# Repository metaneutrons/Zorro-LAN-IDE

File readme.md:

# Zorro-LAN-IDE
 
This is a Zorro-expansion card for the big Amigas (A2000/300/4000 or A500 with Zorro-interface). It has a SANAII-compatible Ethernet driver, an AT-BUS compatible IDE controller and a clockport for variuous expansions like a RapidRoard from Individual Computers.

Here is a pic of the first revision:

All components are Autoconfig. The FastEthernet is based on a ENC624J600 lan chip. The clockport is compatible to A600/A1200 ones but resides at a different address. The IDE works from Kickstart 1.3 to 3.1.4 !

At present there are two firmwares: One for Zorro2, which runs in every Amiga with Zorro-Sots and one for A3000/4000, which puts the LAN-Chip into a Zorro3 environment. The while the Zorro2 variant can transfer 3.5mb/s at most the Zorro3-variant has a significantly faster LAN<->Amiga interface of 6-7mb/sec. Please note that these RAW data transfer numbers are not the only factor in LAN performance on Amiga and that the actual observed speeds with TCP transfers are in the range of 1-2 MB/s (depending on IP stack and CPU). 

Here is a pic of the current board revision:

## Things to improve

* The second revision already adresses the issues of the Zorro3-incompatible IDE-Interface.
* There is no Z2/Z3 combo firmware, yet.
* The RJ45-breakout (actually it's a MagJack with build in transceiver) of the 2nd revision looks bad 

**DISCLAIMER!!!!**  
**THIS IS A HOBBYIST PROJECT! I'M NOT RESPONSIBLE IF IT DOESN'T WORK OR DESTROYS YOUR VALUABLE DATA!**

## License
All sources published under GNU GENERAL PUBLIC LICENSE V2.0

## Theory of operation
* This PCB has four layers and consists of a Xilinx XC95288XL, a bootrom and some bus bufferes for the IDE port, a clockport and a ENC624J600 including a RJ45-connector with integrated receiver. 

* The CPLD does four things:
    * It makes the Autoconfig for the IDE, the clockport and the LAN-chip
    * It adapts the LAN Chip to Zorro2/3 and does necessary byte swapping, so the Amiga can linearely access the whole chip.
    * It acesses the clockport
    * It controlls the IDE

## How to make the clockport work with a RapidRoad?

Make sure you connected the cable the right way! There is no "standarized way". So the easiest thing is to find out on the RapidRoad side on which row of the clockport the two outer pins are ground. These Pins mus run to the row of the Zorro-LAN-IDE-CP-card where the squared solder-hole is located. *Please triple check the cable with a multimeter! Wrong polarity of the cable can cause damage to your hardware!* 
Now you have to set up the driver to look for a clockport at the address of the expansion board. The address can be figured out by the system tool "ShowConfig" (Manufactor id: 2588 Product: 124). 
However, there is work on a software solution, that the RapidRoad finds itself automatically!

## What is in this repository?
This repository consists of several directories:

* Bilder: Some pictures of this project
* Doku: Some documentation and datasheets. Mainly for the ENC624J600
* Driver: Here is the driver developped by Henryk Richter
* Logic: Here the code, project files and pin-assignments for the CPLD is stored. There are two versions: 
* PCB: The board, schematic and bill of material (BOM) are in this directory. 
* root directory: the readme

## How to open the PCB-files?
You find the eagle board and schematic files (brd/sch) for the pcb. The software can be [downloaded](https://www.autodesk.com/products/eagle/overview) for free after registration. KiCad can import these files too. But importers are not 100% reliable... 

## How to make a PCB?
You can generate Gerber-files from the brd files according to the specs of your PCB-manufactor. Some specs: min trace width: 0.15mm/6mil, min trace dist: 0.15mm/6mil, min drill: 0.3mm

**ATTENTION: THE PCB has 4 layers!**

## How to get the parts?
Most parts can be found on digikey or mouser or a parts supplier of your choice.
A list of parts is found in the file [ZORRO-LAN-IDE-CP-V2E.txt](https://gitlab.com/MHeinrichs/Zorro-LAN-IDE/raw/master/PCB/ZORRO-LAN-IDE-CP-V2E.txt)

## How to programm the board?
The CPLD must be programmed via Xilinx IMPACT and an apropriate JTAG-dongle. The JED-File is provided. 

## It doesn't work! How to I get help?
For support visit the [a1k-forum](https://www.a1k.org/forum/showthread.php?t=56940). Yes, you need to register and it's German, but writing in English is accepted. For bug-reports write a ticket here ;).

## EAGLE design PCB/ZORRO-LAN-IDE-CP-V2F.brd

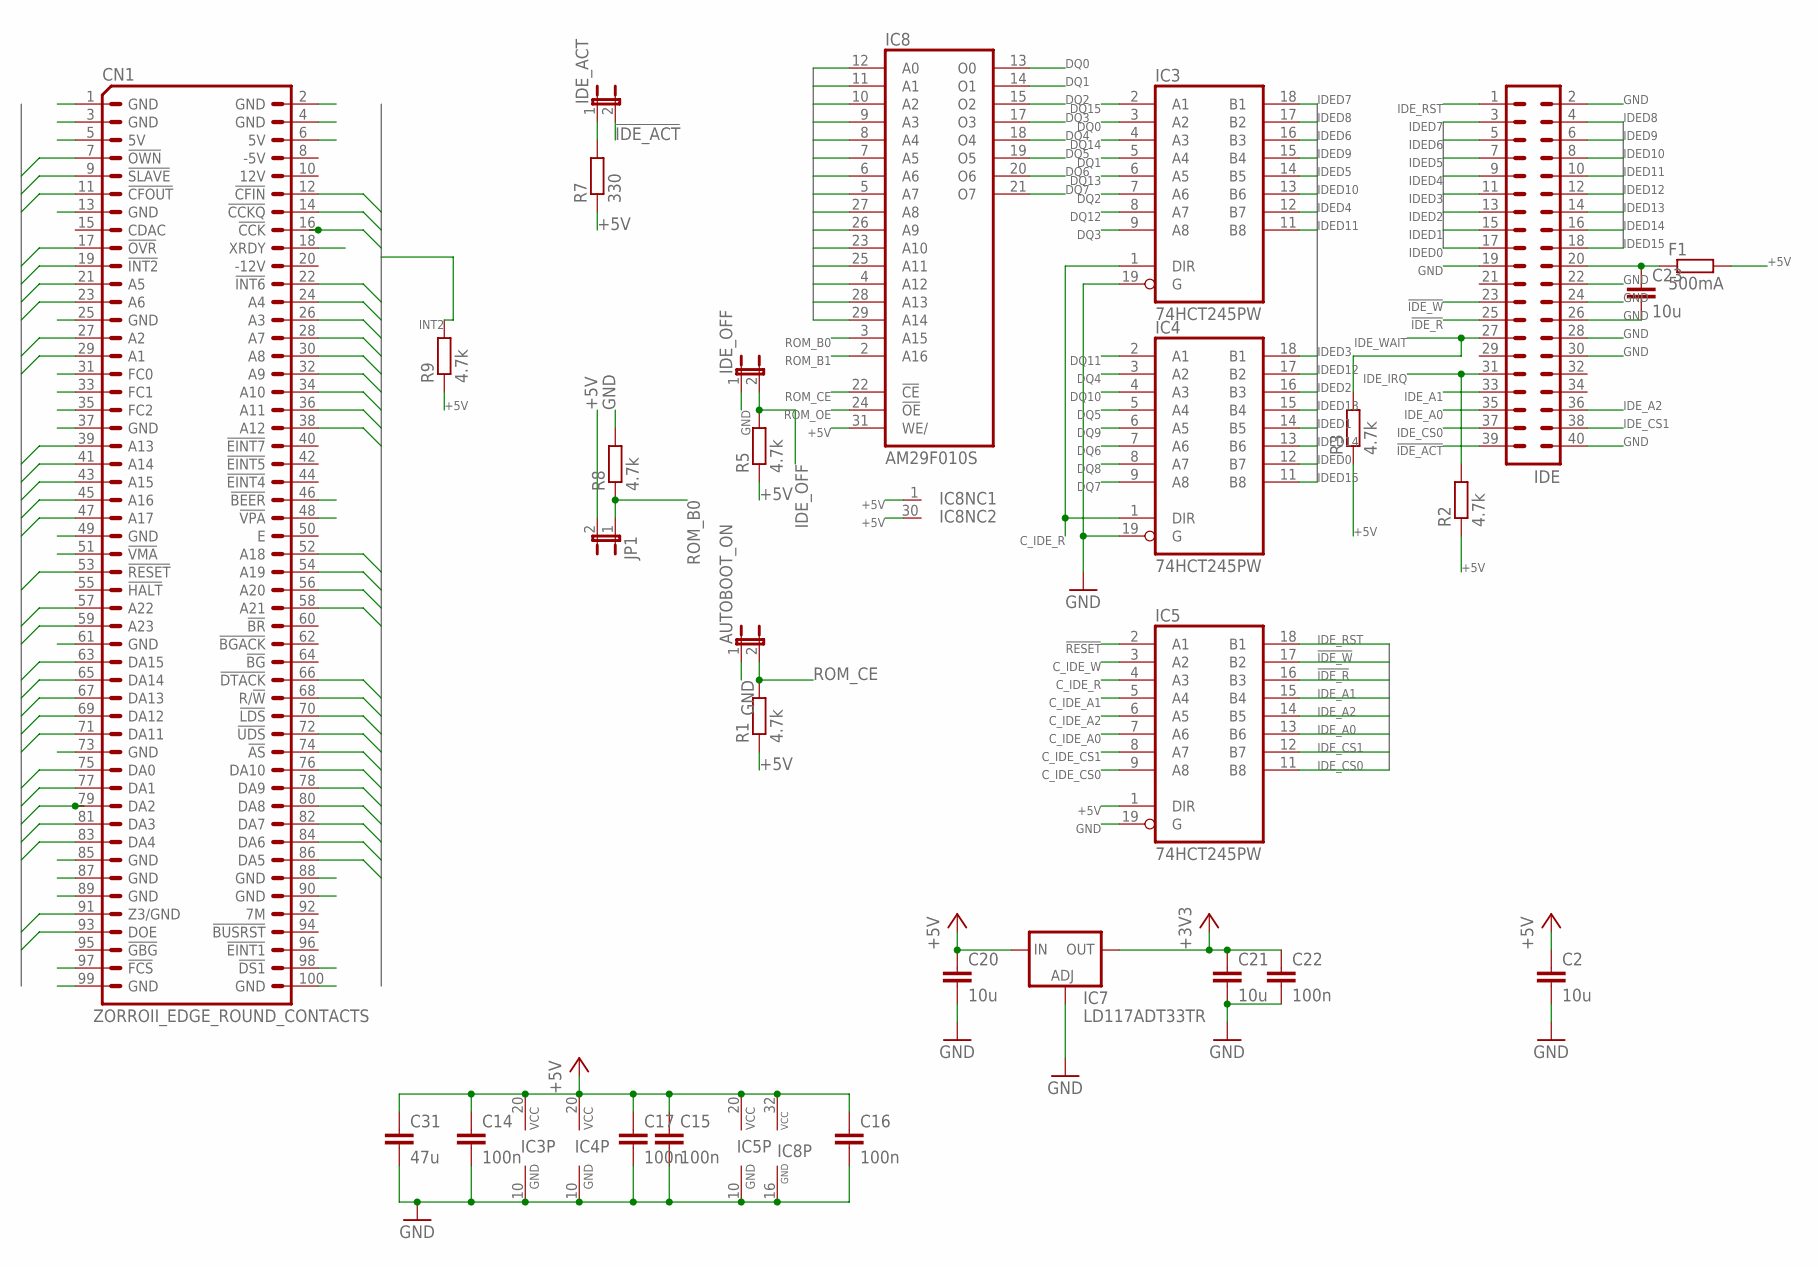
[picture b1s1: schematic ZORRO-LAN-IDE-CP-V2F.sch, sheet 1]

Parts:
AUTOBOOT_ON: JP1E; JP1
C2, C23: 10u; C0805K
C14, C15, C16, C17, C22: 100n; C0603K
C20: 10u; C1206K
C21: 10u; C1210K
C31: 47u; C1206K
CN1: ZORROII_EDGE_ROUND_CONTACTS; LKONT_50_R
F1: 500mA; R2512
IC3, IC4, IC5: 74HCT245PW; TSSOP20
IC7: LD117ADT33TR; DPACK
IC8: AM29F010S; PLCC-SR32
IDE: ML40
IDE_ACT: JP1E; JP1
IDE_OFF: JP1E; JP1
JP1: JP1E; JP1
R1, R2, R3, R5, R8, R9: 4.7k; R0603
R7: 330; R0603

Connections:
!AS: CN1.74 (!AS!); also elsewhere on the board
!BERR: CN1.46 (!BEER!); also elsewhere on the board
!CFIN: CN1.12 (!CFIN!); also elsewhere on the board
!CFOUT: CN1.11 (!CFOUT!); also elsewhere on the board
!DS0: CN1.51 (!VMA!); also elsewhere on the board
!DS1: CN1.98 (!DS1!); also elsewhere on the board
!DTACK: CN1.66 (!DTACK!); also elsewhere on the board
!FCS: CN1.97 (!FCS!); also elsewhere on the board
!IDE_ACT: IDE.39, IDE_ACT.2
!IDE_R: IC5.16 (B3), IDE.25
!IDE_W: IC5.17 (B2), IDE.23
!LDS: CN1.70 (!LDS!); also elsewhere on the board
!MTACK: CN1.48 (!VPA!); also elsewhere on the board
!MTCR: CN1.18 (XRDY); also elsewhere on the board
!OVR: CN1.17 (!OVR!); also elsewhere on the board
!OWN: CN1.7 (!OWN!); also elsewhere on the board
!RESET: CN1.53 (!RESET!), IC5.2 (A1); also elsewhere on the board
!SLAVE: CN1.9 (!SLAVE!); also elsewhere on the board
!UDS: CN1.72 (!UDS!); also elsewhere on the board
+3V3: C21.1, C22.1, IC7.4 (OUT); also elsewhere on the board
+5V: C2.1, C14.1, C15.1, C16.1, C17.1, C20.1, C31.1, CN1.5 (5V), CN1.6 (5V), F1.2, IC3.20 (VCC), IC4.20 (VCC), IC5.1 (DIR), IC5.20 (VCC), IC7.3 (IN), IC8.1 (NC), IC8.30 (NC), IC8.31 (WE/), IC8.32 (VCC), JP1.2, R1.1, R2.1, R3.1, R5.1, R7.1, R9.1; also elsewhere on the board
A1: CN1.29 (A1), IC8.12 (A0); also elsewhere on the board
A2: CN1.27 (A2), IC8.11 (A1); also elsewhere on the board
A3: CN1.26 (A3), IC8.10 (A2); also elsewhere on the board
A4: CN1.24 (A4), IC8.9 (A3); also elsewhere on the board
A5: CN1.21 (A5), IC8.8 (A4); also elsewhere on the board
A6: CN1.23 (A6), IC8.7 (A5); also elsewhere on the board
A7: CN1.28 (A7), IC8.6 (A6); also elsewhere on the board
A8: CN1.30 (A8), IC8.5 (A7); also elsewhere on the board
A9: CN1.32 (A9), IC8.27 (A8); also elsewhere on the board
A10: CN1.34 (A10), IC8.26 (A9); also elsewhere on the board
A11: CN1.36 (A11), IC8.23 (A10); also elsewhere on the board
A12: CN1.38 (A12), IC8.25 (A11); also elsewhere on the board
A13: CN1.39 (A13), IC8.4 (A12); also elsewhere on the board
A14: CN1.41 (A14), IC8.28 (A13); also elsewhere on the board
A15: CN1.43 (A15), IC8.29 (A14); also elsewhere on the board
A16: CN1.45 (A16); also elsewhere on the board
A17: CN1.47 (A17); also elsewhere on the board
A18: CN1.52 (A18); also elsewhere on the board
A19: CN1.54 (A19); also elsewhere on the board
A20: CN1.56 (A20); also elsewhere on the board
A21: CN1.58 (A21); also elsewhere on the board
A22: CN1.57 (A22); also elsewhere on the board
A23: CN1.59 (A23); also elsewhere on the board
C1: CN1.14 (!CCKQ!); also elsewhere on the board
C3: CN1.16 (!CCK!); also elsewhere on the board
C_IDE_A0: IC5.7 (A6); also elsewhere on the board
C_IDE_A1: IC5.5 (A4); also elsewhere on the board
C_IDE_A2: IC5.6 (A5); also elsewhere on the board
C_IDE_CS0: IC5.9 (A8); also elsewhere on the board
C_IDE_CS1: IC5.8 (A7); also elsewhere on the board
C_IDE_R: IC3.1 (DIR), IC4.1 (DIR), IC5.4 (A3); also elsewhere on the board
C_IDE_W: IC5.3 (A2); also elsewhere on the board
D0: CN1.75 (DA0); also elsewhere on the board
D1: CN1.77 (DA1); also elsewhere on the board
D2: CN1.79 (DA2); also elsewhere on the board
D3: CN1.81 (DA3); also elsewhere on the board
D4: CN1.83 (DA4); also elsewhere on the board
D5: CN1.86 (DA5); also elsewhere on the board
D6: CN1.84 (DA6); also elsewhere on the board
D7: CN1.82 (DA7); also elsewhere on the board
D8: CN1.80 (DA8); also elsewhere on the board
D9: CN1.78 (DA9); also elsewhere on the board
D10: CN1.76 (DA10); also elsewhere on the board
D11: CN1.71 (DA11); also elsewhere on the board
D12: CN1.69 (DA12); also elsewhere on the board
D13: CN1.67 (DA13); also elsewhere on the board
D14: CN1.65 (DA14); also elsewhere on the board
D15: CN1.63 (DA15); also elsewhere on the board
DOE: CN1.93 (DOE); also elsewhere on the board
DQ0: IC3.3 (A2), IC8.13 (O0); also elsewhere on the board
DQ1: IC3.5 (A4), IC8.14 (O1); also elsewhere on the board
DQ2: IC3.7 (A6), IC8.15 (O2); also elsewhere on the board
DQ3: IC3.9 (A8), IC8.17 (O3); also elsewhere on the board
DQ4: IC4.3 (A2), IC8.18 (O4); also elsewhere on the board
DQ5: IC4.5 (A4), IC8.19 (O5); also elsewhere on the board
DQ6: IC4.7 (A6), IC8.20 (O6); also elsewhere on the board
DQ7: IC4.9 (A8), IC8.21 (O7); also elsewhere on the board
DQ8: IC4.8 (A7); also elsewhere on the board
DQ9: IC4.6 (A5); also elsewhere on the board
DQ10: IC4.4 (A3); also elsewhere on the board
DQ11: IC4.2 (A1); also elsewhere on the board
DQ12: IC3.8 (A7); also elsewhere on the board
DQ13: IC3.6 (A5); also elsewhere on the board
DQ14: IC3.4 (A3); also elsewhere on the board
DQ15: IC3.2 (A1); also elsewhere on the board
FC0: CN1.31 (FC0)
FC1: CN1.33 (FC1)
FC2: CN1.35 (FC2)
GND: AUTOBOOT_ON.1, C2.2, C14.2, C15.2, C16.2, C17.2, C20.2, C21.2, C22.2, C23.2, C31.2, CN1.1 (GND), CN1.2 (GND), CN1.3 (GND), CN1.4 (GND), CN1.13 (GND), CN1.25 (GND), CN1.37 (GND), CN1.49 (GND), CN1.61 (GND), CN1.73 (GND), CN1.85 (GND), CN1.87 (GND), CN1.88 (GND), CN1.89 (GND), CN1.90 (GND), CN1.99 (GND), CN1.100 (GND), IC3.10 (GND), IC3.19 (G), IC4.10 (GND), IC4.19 (G), IC5.10 (GND), IC5.19 (G), IC7.1 (ADJ), IC8.16 (GND), IDE.2, IDE.19, IDE.22, IDE.24, IDE.26, IDE.28, IDE.30, IDE.40, IDE_OFF.1, R8.2; also elsewhere on the board
IDED0: IC4.12 (B7), IDE.17
IDED1: IC4.14 (B5), IDE.15
IDED2: IC4.16 (B3), IDE.13
IDED3: IC4.18 (B1), IDE.11
IDED4: IC3.12 (B7), IDE.9
IDED5: IC3.14 (B5), IDE.7
IDED6: IC3.16 (B3), IDE.5
IDED7: IC3.18 (B1), IDE.3
IDED8: IC3.17 (B2), IDE.4
IDED9: IC3.15 (B4), IDE.6
IDED10: IC3.13 (B6), IDE.8
IDED11: IC3.11 (B8), IDE.10
IDED12: IC4.17 (B2), IDE.12
IDED13: IC4.15 (B4), IDE.14
IDED14: IC4.13 (B6), IDE.16
IDED15: IC4.11 (B8), IDE.18
IDE_A0: IC5.13 (B6), IDE.35
IDE_A1: IC5.15 (B4), IDE.33
IDE_A2: IC5.14 (B5), IDE.36
IDE_CS0: IC5.11 (B8), IDE.37
IDE_CS1: IC5.12 (B7), IDE.38
IDE_IRQ: IDE.31, R2.2
IDE_OFF: IDE_OFF.2, R5.2; also elsewhere on the board
IDE_RST: IC5.18 (B1), IDE.1; also elsewhere on the board
IDE_WAIT: IDE.27, R3.2; also elsewhere on the board
INT2: CN1.19 (!INT2!), R9.2; also elsewhere on the board
INT6: CN1.22 (!INT6!); also elsewhere on the board
KEY_PIN_POWER: C23.1, F1.1, IDE.20
unnamed: IDE_ACT.1, R7.2
R/W: CN1.68 (R/!W!); also elsewhere on the board
ROM_B0: IC8.3 (A15), JP1.1, R8.1; also elsewhere on the board
ROM_B1: IC8.2 (A16); also elsewhere on the board
ROM_CE: AUTOBOOT_ON.2, IC8.22 (!CE), R1.2
ROM_OE: IC8.24 (!OE); also elsewhere on the board
Z3: CN1.91 (Z3/GND); also elsewhere on the board

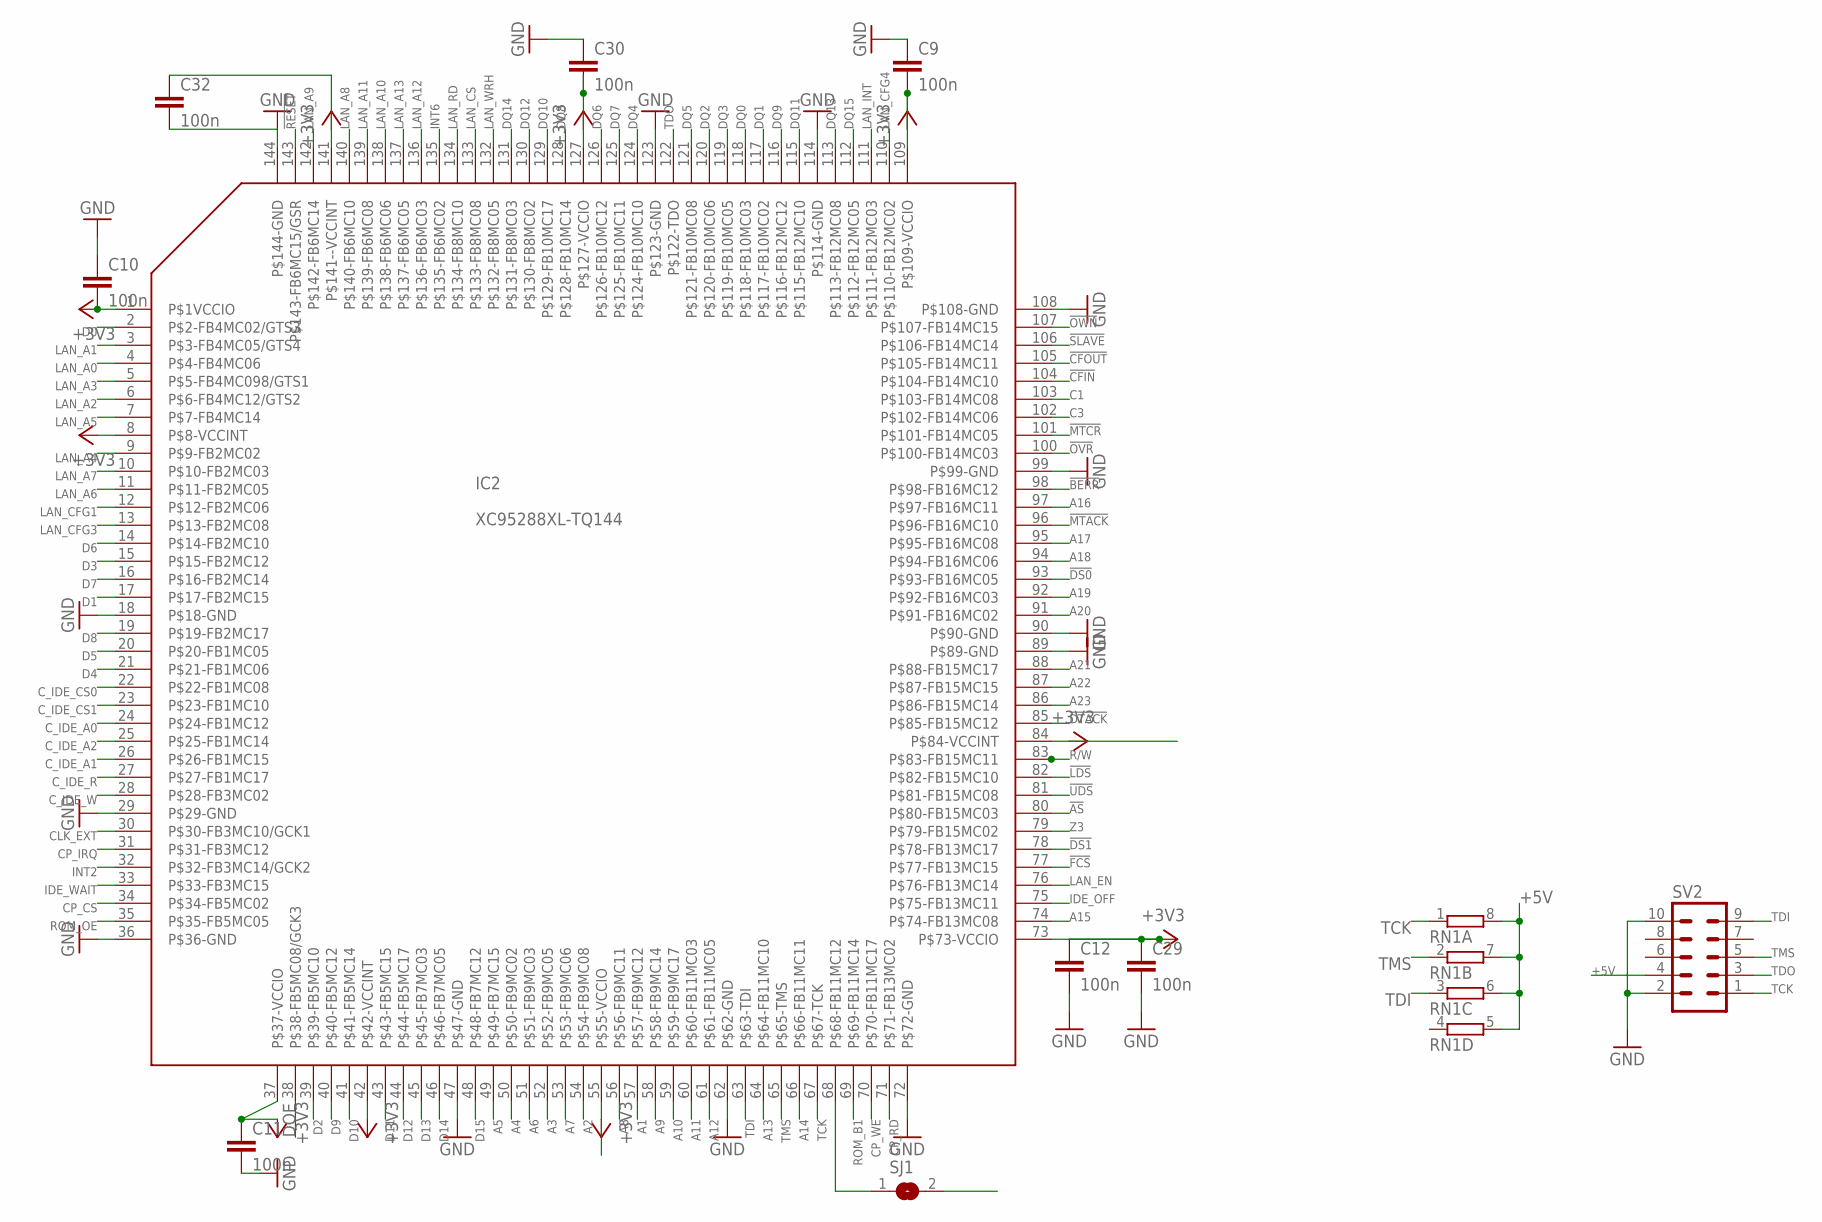
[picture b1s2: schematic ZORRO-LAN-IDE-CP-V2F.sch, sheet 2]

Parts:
C9, C10, C11, C12, C29, C30, C32: 100n; C0603K
IC2: XC95288XL-TQ144; TQFP144
RN1: 4R-NCAY16; CAY16
SJ1: SJ
SV2: ML10L

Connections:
!AS: IC2.80 (P$80-FB15MC03); also elsewhere on the board
!BERR: IC2.98 (P$98-FB16MC12); also elsewhere on the board
!CFIN: IC2.104 (P$104-FB14MC10); also elsewhere on the board
!CFOUT: IC2.105 (P$105-FB14MC11); also elsewhere on the board
!DS0: IC2.93 (P$93-FB16MC05); also elsewhere on the board
!DS1: IC2.78 (P$78-FB13MC17); also elsewhere on the board
!DTACK: IC2.85 (P$85-FB15MC12); also elsewhere on the board
!FCS: IC2.77 (P$77-FB13MC15); also elsewhere on the board
!LDS: IC2.82 (P$82-FB15MC10); also elsewhere on the board
!MTACK: IC2.96 (P$96-FB16MC10); also elsewhere on the board
!MTCR: IC2.101 (P$101-FB14MC05); also elsewhere on the board
!OVR: IC2.100 (P$100-FB14MC03); also elsewhere on the board
!OWN: IC2.107 (P$107-FB14MC15); also elsewhere on the board
!RESET: IC2.143 (P$143-FB6MC15/GSR); also elsewhere on the board
!SLAVE: IC2.106 (P$106-FB14MC14); also elsewhere on the board
!UDS: IC2.81 (P$81-FB15MC08); also elsewhere on the board
+3V3: C9.2, C10.2, C11.1, C12.1, C29.1, C30.2, C32.1, IC2.1 (P$1VCCIO), IC2.8 (P$8-VCCINT), IC2.37 (P$37-VCCIO), IC2.42 (P$42-VCCINT), IC2.55 (P$55-VCCIO), IC2.73 (P$73-VCCIO), IC2.84 (P$84-VCCINT), IC2.109 (P$109-VCCIO), IC2.127 (P$127-VCCIO), IC2.141 (P$141--VCCINT); also elsewhere on the board
+5V: RN1.5 (2), RN1.6 (2), RN1.7 (2), RN1.8 (2), SV2.4; also elsewhere on the board
A1: IC2.57 (P$57-FB9MC12); also elsewhere on the board
A2: IC2.54 (P$54-FB9MC08); also elsewhere on the board
A3: IC2.52 (P$52-FB9MC05); also elsewhere on the board
A4: IC2.50 (P$50-FB9MC02); also elsewhere on the board
A5: IC2.49 (P$49-FB7MC15); also elsewhere on the board
A6: IC2.51 (P$51-FB9MC03); also elsewhere on the board
A7: IC2.53 (P$53-FB9MC06); also elsewhere on the board
A8: IC2.56 (P$56-FB9MC11); also elsewhere on the board
A9: IC2.58 (P$58-FB9MC14); also elsewhere on the board
A10: IC2.59 (P$59-FB9MC17); also elsewhere on the board
A11: IC2.60 (P$60-FB11MC03); also elsewhere on the board
A12: IC2.61 (P$61-FB11MC05); also elsewhere on the board
A13: IC2.64 (P$64-FB11MC10); also elsewhere on the board
A14: IC2.66 (P$66-FB11MC11); also elsewhere on the board
A15: IC2.74 (P$74-FB13MC08); also elsewhere on the board
A16: IC2.97 (P$97-FB16MC11); also elsewhere on the board
A17: IC2.95 (P$95-FB16MC08); also elsewhere on the board
A18: IC2.94 (P$94-FB16MC06); also elsewhere on the board
A19: IC2.92 (P$92-FB16MC03); also elsewhere on the board
A20: IC2.91 (P$91-FB16MC02); also elsewhere on the board
A21: IC2.88 (P$88-FB15MC17); also elsewhere on the board
A22: IC2.87 (P$87-FB15MC15); also elsewhere on the board
A23: IC2.86 (P$86-FB15MC14); also elsewhere on the board
C1: IC2.103 (P$103-FB14MC08); also elsewhere on the board
C3: IC2.102 (P$102-FB14MC06); also elsewhere on the board
CLK_EXT: IC2.30 (P$30-FB3MC10/GCK1); also elsewhere on the board
CP_CS: IC2.34 (P$34-FB5MC02); also elsewhere on the board
CP_IRQ: IC2.31 (P$31-FB3MC12); also elsewhere on the board
CP_RD: IC2.71 (P$71-FB13MC02); also elsewhere on the board
CP_WE: IC2.70 (P$70-FB11MC17); also elsewhere on the board
C_IDE_A0: IC2.24 (P$24-FB1MC12); also elsewhere on the board
C_IDE_A1: IC2.26 (P$26-FB1MC15); also elsewhere on the board
C_IDE_A2: IC2.25 (P$25-FB1MC14); also elsewhere on the board
C_IDE_CS0: IC2.22 (P$22-FB1MC08); also elsewhere on the board
C_IDE_CS1: IC2.23 (P$23-FB1MC10); also elsewhere on the board
C_IDE_R: IC2.27 (P$27-FB1MC17); also elsewhere on the board
C_IDE_W: IC2.28 (P$28-FB3MC02); also elsewhere on the board
D0: IC2.2 (P$2-FB4MC02/GTS3); also elsewhere on the board
D1: IC2.17 (P$17-FB2MC15); also elsewhere on the board
D2: IC2.39 (P$39-FB5MC10); also elsewhere on the board
D3: IC2.15 (P$15-FB2MC12); also elsewhere on the board
D4: IC2.21 (P$21-FB1MC06); also elsewhere on the board
D5: IC2.20 (P$20-FB1MC05); also elsewhere on the board
D6: IC2.14 (P$14-FB2MC10); also elsewhere on the board
D7: IC2.16 (P$16-FB2MC14); also elsewhere on the board
D8: IC2.19 (P$19-FB2MC17); also elsewhere on the board
D9: IC2.40 (P$40-FB5MC12); also elsewhere on the board
D10: IC2.41 (P$41-FB5MC14); also elsewhere on the board
D11: IC2.43 (P$43-FB5MC15); also elsewhere on the board
D12: IC2.44 (P$44-FB5MC17); also elsewhere on the board
D13: IC2.45 (P$45-FB7MC03); also elsewhere on the board
D14: IC2.46 (P$46-FB7MC05); also elsewhere on the board
D15: IC2.48 (P$48-FB7MC12); also elsewhere on the board
DOE: IC2.38 (P$38-FB5MC08/GCK3); also elsewhere on the board
DQ0: IC2.118 (P$118-FB10MC03); also elsewhere on the board
DQ1: IC2.117 (P$117-FB10MC02); also elsewhere on the board
DQ2: IC2.120 (P$120-FB10MC06); also elsewhere on the board
DQ3: IC2.119 (P$119-FB10MC05); also elsewhere on the board
DQ4: IC2.124 (P$124-FB10MC10); also elsewhere on the board
DQ5: IC2.121 (P$121-FB10MC08); also elsewhere on the board
DQ6: IC2.126 (P$126-FB10MC12); also elsewhere on the board
DQ7: IC2.125 (P$125-FB10MC11); also elsewhere on the board
DQ8: IC2.128 (P$128-FB10MC14); also elsewhere on the board
DQ9: IC2.116 (P$116-FB12MC12); also elsewhere on the board
DQ10: IC2.129 (P$129-FB10MC17); also elsewhere on the board
DQ11: IC2.115 (P$115-FB12MC10); also elsewhere on the board
DQ12: IC2.130 (P$130-FB8MC02); also elsewhere on the board
DQ13: IC2.113 (P$113-FB12MC08); also elsewhere on the board
DQ14: IC2.131 (P$131-FB8MC03); also elsewhere on the board
DQ15: IC2.112 (P$112-FB12MC05); also elsewhere on the board
GND: C9.1, C10.1, C11.2, C12.2, C29.2, C30.1, C32.2, IC2.18 (P$18-GND), IC2.29 (P$29-GND), IC2.36 (P$36-GND), IC2.47 (P$47-GND), IC2.62 (P$62-GND), IC2.72 (P$72-GND), IC2.89 (P$89-GND), IC2.90 (P$90-GND), IC2.99 (P$99-GND), IC2.108 (P$108-GND), IC2.114 (P$114-GND), IC2.123 (P$123-GND), IC2.144 (P$144-GND), SV2.2, SV2.10; also elsewhere on the board
IDE_OFF: IC2.75 (P$75-FB13MC11); also elsewhere on the board
IDE_WAIT: IC2.33 (P$33-FB3MC15); also elsewhere on the board
INT2: IC2.32 (P$32-FB3MC14/GCK2); also elsewhere on the board
INT6: IC2.135 (P$135-FB6MC02); also elsewhere on the board
LAN_A0: IC2.4 (P$4-FB4MC06); also elsewhere on the board
LAN_A1: IC2.3 (P$3-FB4MC05/GTS4); also elsewhere on the board
LAN_A2: IC2.6 (P$6-FB4MC12/GTS2); also elsewhere on the board
LAN_A3: IC2.5 (P$5-FB4MC098/GTS1); also elsewhere on the board
LAN_A4: IC2.9 (P$9-FB2MC02); also elsewhere on the board
LAN_A5: IC2.7 (P$7-FB4MC14); also elsewhere on the board
LAN_A6: IC2.11 (P$11-FB2MC05); also elsewhere on the board
LAN_A7: IC2.10 (P$10-FB2MC03); also elsewhere on the board
LAN_A8: IC2.140 (P$140-FB6MC10); also elsewhere on the board
LAN_A9: IC2.142 (P$142-FB6MC14); also elsewhere on the board
LAN_A10: IC2.138 (P$138-FB6MC06); also elsewhere on the board
LAN_A11: IC2.139 (P$139-FB6MC08); also elsewhere on the board
LAN_A12: IC2.136 (P$136-FB6MC03); also elsewhere on the board
LAN_A13: IC2.137 (P$137-FB6MC05); also elsewhere on the board
LAN_CFG1: IC2.12 (P$12-FB2MC06)
LAN_CFG3: IC2.13 (P$13-FB2MC08)
LAN_CFG4: IC2.110 (P$110-FB12MC02)
LAN_CS: IC2.133 (P$133-FB8MC08); also elsewhere on the board
LAN_EN: IC2.76 (P$76-FB13MC14); also elsewhere on the board
LAN_INT: IC2.111 (P$111-FB12MC03); also elsewhere on the board
LAN_RD: IC2.134 (P$134-FB8MC10); also elsewhere on the board
LAN_WRH: IC2.132 (P$132-FB8MC05); also elsewhere on the board
unnamed: IC2.68 (P$68-FB11MC12), SJ1.1
R/W: IC2.83 (P$83-FB15MC11); also elsewhere on the board
ROM_B0: SJ1.2; also elsewhere on the board
ROM_B1: IC2.69 (P$69-FB11MC14); also elsewhere on the board
ROM_OE: IC2.35 (P$35-FB5MC05); also elsewhere on the board
TCK: IC2.67 (P$67-TCK), RN1.1, SV2.1
TDI: IC2.63 (P$63-TDI), RN1.3 (1), SV2.9
TDO: IC2.122 (P$122-TDO), SV2.3
TMS: IC2.65 (P$65-TMS), RN1.2 (1), SV2.5
Z3: IC2.79 (P$79-FB15MC02); also elsewhere on the board

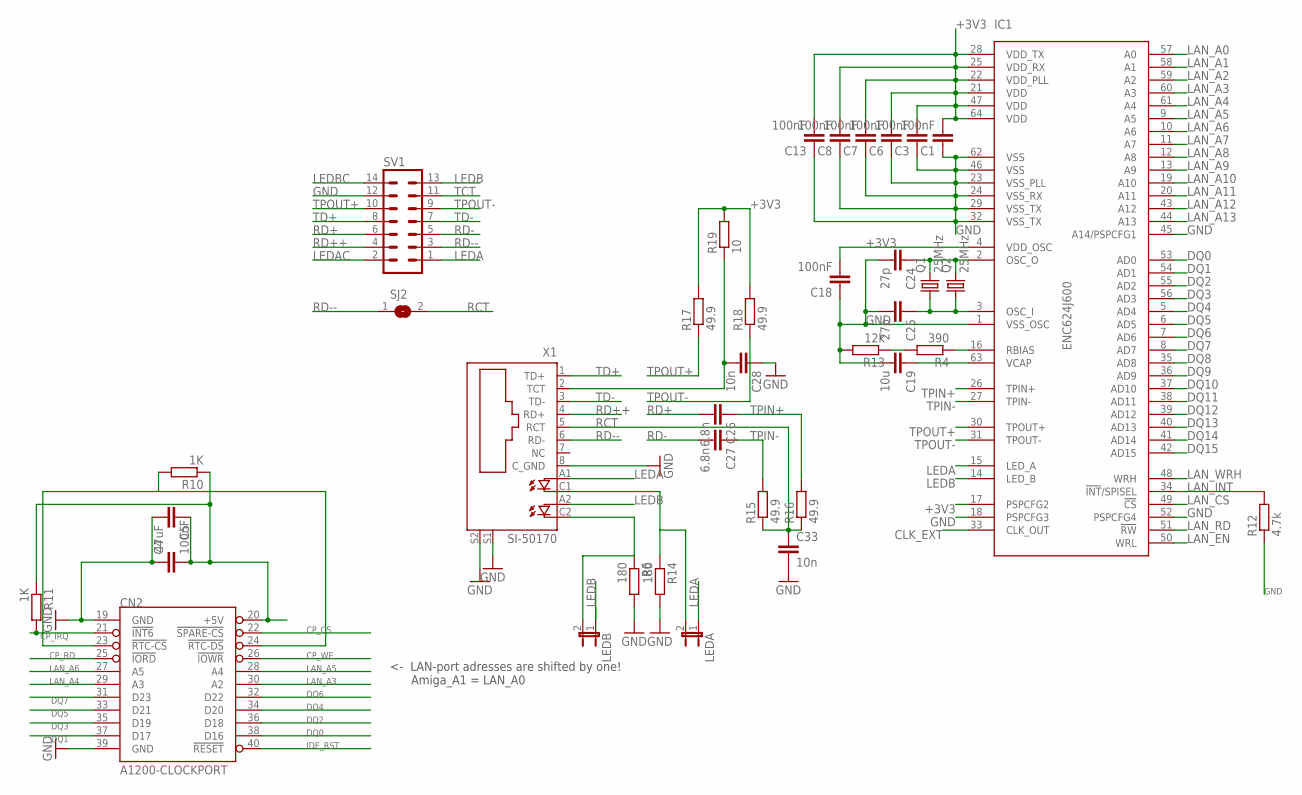
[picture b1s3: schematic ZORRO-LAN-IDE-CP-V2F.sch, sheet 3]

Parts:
C1, C3, C4, C6, C7, C8, C13, C18: 100nF; C0805K
C5: 47uF; C1206K
C19: 10u; C1206K
C24, C25: 27p; C0805K
C26, C27: 6.8n; C0805K
C28, C33: 10n; C0805K
CN2: A1200-CLOCKPORT; CP-2X11-2.00
IC1: ENC624J600; SQFP-S-10X10-64
LEDA: JP1E; JP1
LEDB: JP1E; JP1
Q1: 25MHz; HC18U-V
Q2: 25MHz; HC49UP
R4: 390; R0603
R6, R14: 180; R0603
R10, R11: 1K; R0805
R12: 4.7k; R0603
R13: 12k; R0603
R15, R16, R17, R18: 49.9; R0603
R19: 10; R0603
SJ2: SJ
SV1: ML14
X1: SI-50170

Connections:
+3V3: C1.2, C3.2, C6.2, C7.2, C8.2, C13.2, C18.2, IC1.4 (VDD_OSC), IC1.17 (PSPCFG2), IC1.21 (VDD), IC1.22 (VDD_PLL), IC1.25 (VDD_RX), IC1.28 (VDD_TX), IC1.47 (VDD), IC1.64 (VDD), R17.2, R18.2, R19.2; also elsewhere on the board
+5V: C4.2, C5.1, CN2.20 (+5V), R10.1, R11.1; also elsewhere on the board
CLK_EXT: IC1.33 (CLK_OUT); also elsewhere on the board
CP_CS: CN2.22 (!SPARE-CS); also elsewhere on the board
CP_IRQ: CN2.21 (!INT6), R11.2; also elsewhere on the board
CP_RD: CN2.25 (!IORD); also elsewhere on the board
CP_WE: CN2.26 (!IOWR); also elsewhere on the board
DQ0: CN2.38 (D16), IC1.53 (AD0); also elsewhere on the board
DQ1: CN2.37 (D17), IC1.54 (AD1); also elsewhere on the board
DQ2: CN2.36 (D18), IC1.55 (AD2); also elsewhere on the board
DQ3: CN2.35 (D19), IC1.56 (AD3); also elsewhere on the board
DQ4: CN2.34 (D20), IC1.5 (AD4); also elsewhere on the board
DQ5: CN2.33 (D21), IC1.6 (AD5); also elsewhere on the board
DQ6: CN2.32 (D22), IC1.7 (AD6); also elsewhere on the board
DQ7: CN2.31 (D23), IC1.8 (AD7); also elsewhere on the board
DQ8: IC1.35 (AD8); also elsewhere on the board
DQ9: IC1.36 (AD9); also elsewhere on the board
DQ10: IC1.37 (AD10); also elsewhere on the board
DQ11: IC1.38 (AD11); also elsewhere on the board
DQ12: IC1.39 (AD12); also elsewhere on the board
DQ13: IC1.40 (AD13); also elsewhere on the board
DQ14: IC1.41 (AD14); also elsewhere on the board
DQ15: IC1.42 (AD15); also elsewhere on the board
GND: C1.1, C3.1, C4.1, C5.2, C6.1, C7.1, C8.1, C13.1, C18.1, C19.2, C24.2, C25.2, C28.1, C33.2, CN2.19 (GND), CN2.39 (GND), IC1.1 (VSS_OSC), IC1.18 (PSPCFG3), IC1.23 (VSS_PLL), IC1.24 (VSS_RX), IC1.29 (VSS_TX), IC1.32 (VSS_TX), IC1.45 (A14/PSPCFG1), IC1.46 (VSS), IC1.52 (PSPCFG4), IC1.62 (VSS), R6.2, R12.1, R13.2, R14.2, SV1.12, X1.8 (C_GND), X1.S1, X1.S2; also elsewhere on the board
IDE_RST: CN2.40 (!RESET); also elsewhere on the board
LAN_A0: IC1.57 (A0); also elsewhere on the board
LAN_A1: IC1.58 (A1); also elsewhere on the board
LAN_A2: IC1.59 (A2); also elsewhere on the board
LAN_A3: CN2.30 (A2), IC1.60 (A3); also elsewhere on the board
LAN_A4: CN2.29 (A3), IC1.61 (A4); also elsewhere on the board
LAN_A5: CN2.28 (A4), IC1.9 (A5); also elsewhere on the board
LAN_A6: CN2.27 (A5), IC1.10 (A6); also elsewhere on the board
LAN_A7: IC1.11 (A7); also elsewhere on the board
LAN_A8: IC1.12 (A8); also elsewhere on the board
LAN_A9: IC1.13 (A9); also elsewhere on the board
LAN_A10: IC1.19 (A10); also elsewhere on the board
LAN_A11: IC1.20 (A11); also elsewhere on the board
LAN_A12: IC1.43 (A12); also elsewhere on the board
LAN_A13: IC1.44 (A13); also elsewhere on the board
LAN_CS: IC1.49 (!CS); also elsewhere on the board
LAN_EN: IC1.50 (WRL); also elsewhere on the board
LAN_INT: IC1.34 (!INT!/SPISEL), R12.2; also elsewhere on the board
LAN_RD: IC1.51 (!RW); also elsewhere on the board
LAN_WRH: IC1.48 (WRH); also elsewhere on the board
LEDA: IC1.15 (LED_A), LEDA.1, SV1.1, X1.A1 (A)
LEDAC: LEDA.2, R14.1, SV1.2, X1.C1 (C)
LEDB: IC1.14 (LED_B), LEDB.1, SV1.13, X1.A2 (A1)
LEDBC: LEDB.2, R6.1, SV1.14, X1.C2 (C1)
unnamed: CN2.23 (!RTC-CS), CN2.24 (!RTC-DS), R10.2
unnamed: C19.1, IC1.63 (VCAP)
unnamed: R4.2, R13.1
unnamed: IC1.16 (RBIAS), R4.1
unnamed: C25.1, IC1.3 (OSC_I), Q1.1, Q2.1
unnamed: C24.1, IC1.2 (OSC_O), Q1.2, Q2.2
RCT: C33.1, R15.1, R16.1, SJ2.2, X1.5 (RCT)
RD+: C26.2, SV1.6
RD++: SV1.4, X1.4 (RD+)
RD-: C27.2, SV1.5
RD--: SJ2.1, SV1.3, X1.6 (RD-)
TCT: C28.2, R19.1, SV1.11, X1.2 (TCT)
TD+: SV1.8, X1.1 (TD+)
TD-: SV1.7, X1.3 (TD-)
TPIN+: C26.1, IC1.26 (TPIN+), R16.2
TPIN-: C27.1, IC1.27 (TPIN-), R15.2
TPOUT+: IC1.30 (TPOUT+), R17.1, SV1.10
TPOUT-: IC1.31 (TPOUT-), R18.1, SV1.9

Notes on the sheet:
<- LAN-port adresses are shifted by one! Amiga_A1 = LAN_A0

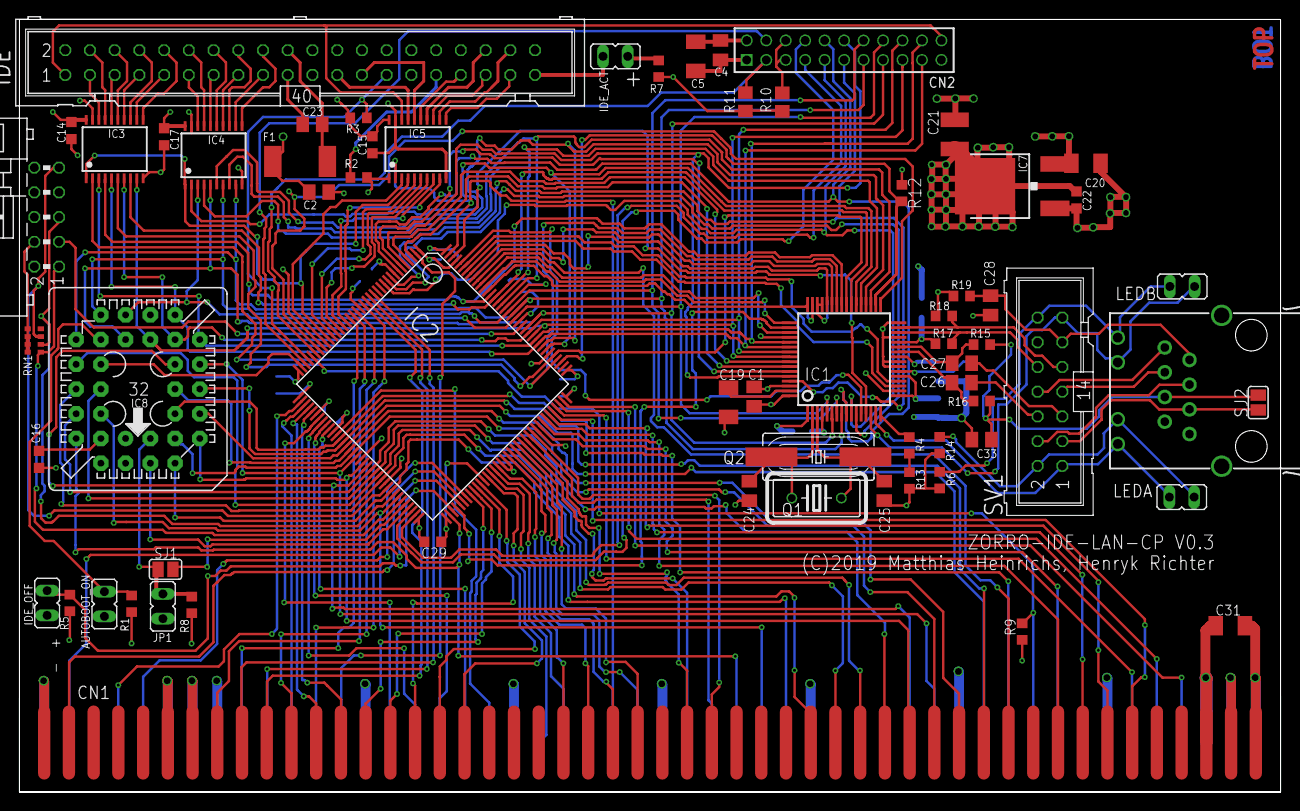
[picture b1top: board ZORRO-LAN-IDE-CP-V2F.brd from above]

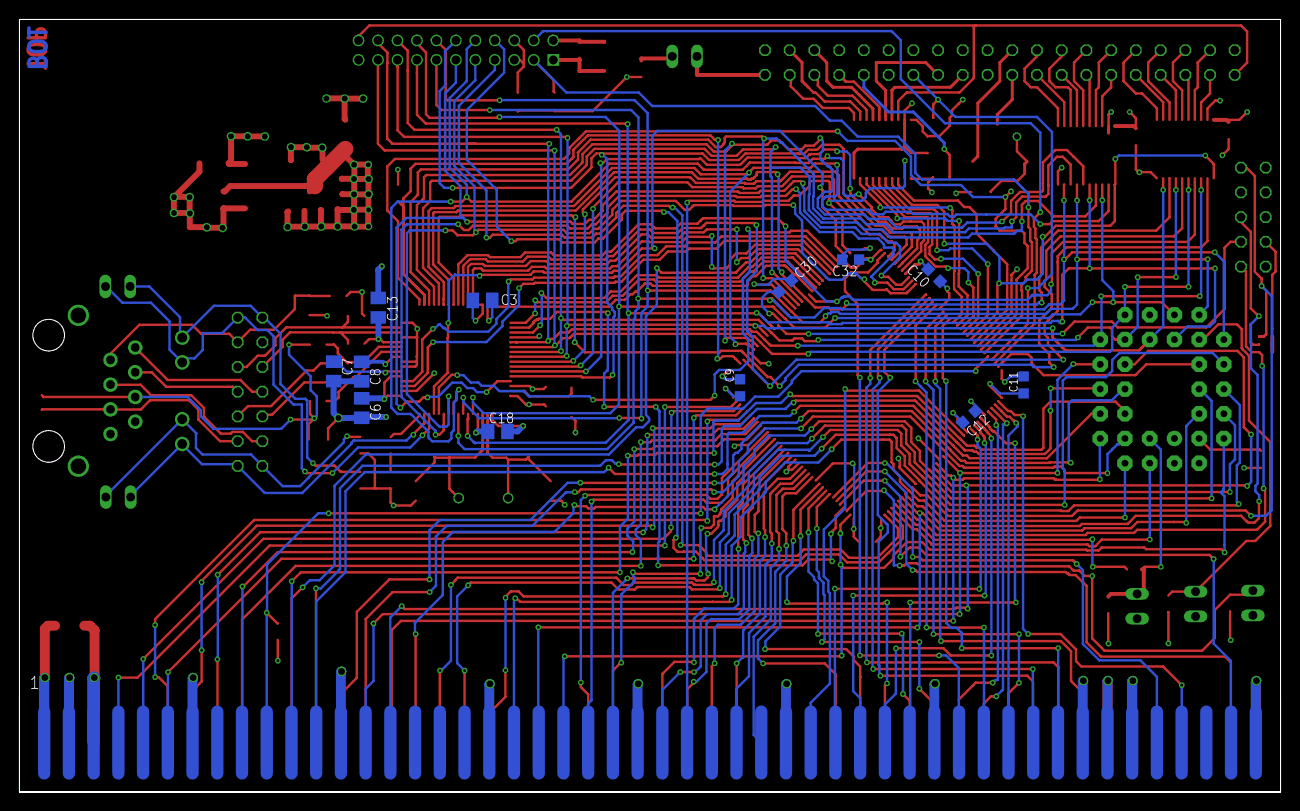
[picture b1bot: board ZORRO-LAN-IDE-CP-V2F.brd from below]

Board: 4 copper layers, 129.5 x 79.4 mm, 77 parts (12 on the bottom side), 173 nets.

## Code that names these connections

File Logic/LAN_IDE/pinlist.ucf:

#PACE: Start of Constraints generated by PACE
#PACE: Start of PACE I/O Pin Assignments
NET "A<10>"  LOC = "P59"  ; 
NET "A<11>"  LOC = "P60"  ; 
NET "A<12>"  LOC = "P61"  ; 
NET "A<13>"  LOC = "P64"  ; 
NET "A<14>"  LOC = "P66"  ; 
NET "A<15>"  LOC = "P74"  ; 
NET "A<16>"  LOC = "P97"  ; 
NET "A<17>"  LOC = "P95"  ; 
NET "A<18>"  LOC = "P94"  ; 
NET "A<19>"  LOC = "P92"  ; 
NET "A<1>"  LOC = "P57"  ; 
NET "A<20>"  LOC = "P91"  ; 
NET "A<21>"  LOC = "P88"  ; 
NET "A<22>"  LOC = "P87"  ; 
NET "A<23>"  LOC = "P86"  ; 
NET "A<2>"  LOC = "P54"  ; 
NET "A<3>"  LOC = "P52"  ; 
NET "A<4>"  LOC = "P50"  ; 
NET "A<5>"  LOC = "P49"  ; 
NET "A<6>"  LOC = "P51"  ; 
NET "A<7>"  LOC = "P53"  ; 
NET "A<8>"  LOC = "P56"  ; 
NET "A<9>"  LOC = "P58"  ; 
NET "A_LAN<0>"  LOC = "P4"  ;
NET "A_LAN<10>"  LOC = "P138"  ;
NET "A_LAN<11>"  LOC = "P139"  ;
NET "A_LAN<12>"  LOC = "P136"  ;
NET "A_LAN<13>"  LOC = "P137"  ;
NET "A_LAN<1>"  LOC = "P3"  ;
NET "A_LAN<2>"  LOC = "P6"  ;
NET "A_LAN<3>"  LOC = "P5"  ;
NET "A_LAN<4>"  LOC = "P9"  ;
NET "A_LAN<5>"  LOC = "P7"  ;
NET "A_LAN<6>"  LOC = "P11"  ;
NET "A_LAN<7>"  LOC = "P10"  ;
NET "A_LAN<8>"  LOC = "P140"  ;
NET "A_LAN<9>"  LOC = "P142"  ;
NET "AS"  LOC = "P80"  ; 
NET "AUTOBOOT_OFF"  LOC = "P75"  ; 
NET "BERR"  LOC = "P98"  ; 
NET "C1"  LOC = "P103"  ; 
NET "C3"  LOC = "P102"  ; 
NET "CFIN"  LOC = "P104"  ; 
NET "CFOUT"  LOC = "P105"  ; 
NET "CLK_EXT"  LOC = "P30"  ;
NET "CP_CS"  LOC = "P34"  ;
NET "CP_IRQ"  LOC = "P31"  ;
NET "CP_RD"  LOC = "P71"  ;
NET "CP_WE"  LOC = "P70"  ;
NET "D<0>"  LOC = "P2"  ; 
NET "D<10>"  LOC = "P41"  ; 
NET "D<11>"  LOC = "P43"  ; 
NET "D<12>"  LOC = "P44"  ; 
NET "D<13>"  LOC = "P45"  ; 
NET "D<14>"  LOC = "P46"  ; 
NET "D<15>"  LOC = "P48"  ; 
NET "D<1>"  LOC = "P17"  ; 
NET "D<2>"  LOC = "P39"  ; 
NET "D<3>"  LOC = "P15"  ; 
NET "D<4>"  LOC = "P21"  ; 
NET "D<5>"  LOC = "P20"  ; 
NET "D<6>"  LOC = "P14"  ; 
NET "D<7>"  LOC = "P16"  ; 
NET "D<8>"  LOC = "P19"  ; 
NET "D<9>"  LOC = "P40"  ; 
NET "DQ<0>"  LOC = "P118"  ;
NET "DQ<10>"  LOC = "P129"  ;
NET "DQ<11>"  LOC = "P115"  ;
NET "DQ<12>"  LOC = "P130"  ;
NET "DQ<13>"  LOC = "P113"  ;
NET "DQ<14>"  LOC = "P131"  ;
NET "DQ<15>"  LOC = "P112"  ;
NET "DQ<1>"  LOC = "P117"  ;
NET "DQ<2>"  LOC = "P120"  ;
//NET "DQ<2>"  LOC = "P68"  ; //fix for broken Xilinx
NET "DQ<3>"  LOC = "P119"  ;
NET "DQ<4>"  LOC = "P124"  ;
NET "DQ<5>"  LOC = "P121"  ;
//NET "DQ<5>"  LOC = "P38"  ;//fix for broken Xilinx
NET "DQ<6>"  LOC = "P126"  ;
NET "DQ<7>"  LOC = "P125"  ;
NET "DQ<8>"  LOC = "P128"  ;
NET "DQ<9>"  LOC = "P116"  ;
NET "DS0"  LOC = "P93"  ; 
NET "DS1"  LOC = "P78"  ; 
NET "DTACK"  LOC = "P85"  ; 
NET "FCS"  LOC = "P77"  ; 
NET "IDE_A<0>"  LOC = "P24"  ;
NET "IDE_A<1>"  LOC = "P26"  ;
NET "IDE_A<2>"  LOC = "P25"  ;
NET "IDE_CS<0>"  LOC = "P22"  ;
NET "IDE_CS<1>"  LOC = "P23"  ;
NET "IDE_R"  LOC = "P27"  ;
NET "IDE_W"  LOC = "P28"  ;
NET "IDE_WAIT"  LOC = "P33"  ;
NET "INT2_OUT"  LOC = "P32"  ;
NET "LAN_CFG<1>"  LOC = "P12"  ;
NET "LAN_CFG<2>"  LOC = "P135"  ;
NET "LAN_CFG<3>"  LOC = "P13"  ;
NET "LAN_CFG<4>"  LOC = "P110"  ;
NET "LAN_CS"  LOC = "P133"  ;
NET "LAN_WRL"  LOC = "P76"  ; 
NET "LAN_INT"  LOC = "P111"  ;
NET "LAN_RD"  LOC = "P134"  ;
NET "LAN_WRH"  LOC = "P132"  ;
NET "LDS"  LOC = "P82"  ; 
NET "MTACK"  LOC = "P96"  ; 
NET "MTCR"  LOC = "P101"  ; 
NET "OVR"  LOC = "P100"  ; 
NET "OWN"  LOC = "P107"  ; 
NET "RESET"  LOC = "P143"  ;
NET "INT6_OUT"  LOC = "P68"  ;//comment fix for INT6, connect right side of solderpad SJ1 with int6
NET "ROM_B<1>"  LOC = "P69"  ;
NET "ROM_OE"  LOC = "P35"  ;
NET "RW"  LOC = "P83"  ;
NET "SLAVE"  LOC = "P106"  ; 
NET "UDS"  LOC = "P81"  ; 
NET "Z3"  LOC = "P79"  ;
#Created by Constraints Editor (xc95288xl-tq144-10) - 2017/01/26
NET "CLK_EXT" TNM_NET = CLK_EXT;
TIMESPEC TS_CLK_EXT = PERIOD "CLK_EXT" 25 MHz HIGH 50%;
#Created by Constraints Editor (xc95288xl-tq144-10) - 2019/02/24
NET "C1" TNM_NET = C1;
TIMESPEC TS_C1 = PERIOD "C1" 3.5 MHz HIGH 50%;
NET "C3" TNM_NET = C3;
TIMESPEC TS_C3 = PERIOD "C3" 3.5 MHz HIGH 50%;
NET "FCS" TNM_NET = FCS;
TIMESPEC TS_FCS = PERIOD "FCS" 25 MHz HIGH 50%;
NET "AS" TNM_NET = AS;
TIMESPEC TS_AS = PERIOD "AS" 7 MHz HIGH 50%;

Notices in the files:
PCB/ZORRO-LAN-IDE-CP-V2F.brd:
(C)2019 Matthias Heinrichs, Henryk Richter
